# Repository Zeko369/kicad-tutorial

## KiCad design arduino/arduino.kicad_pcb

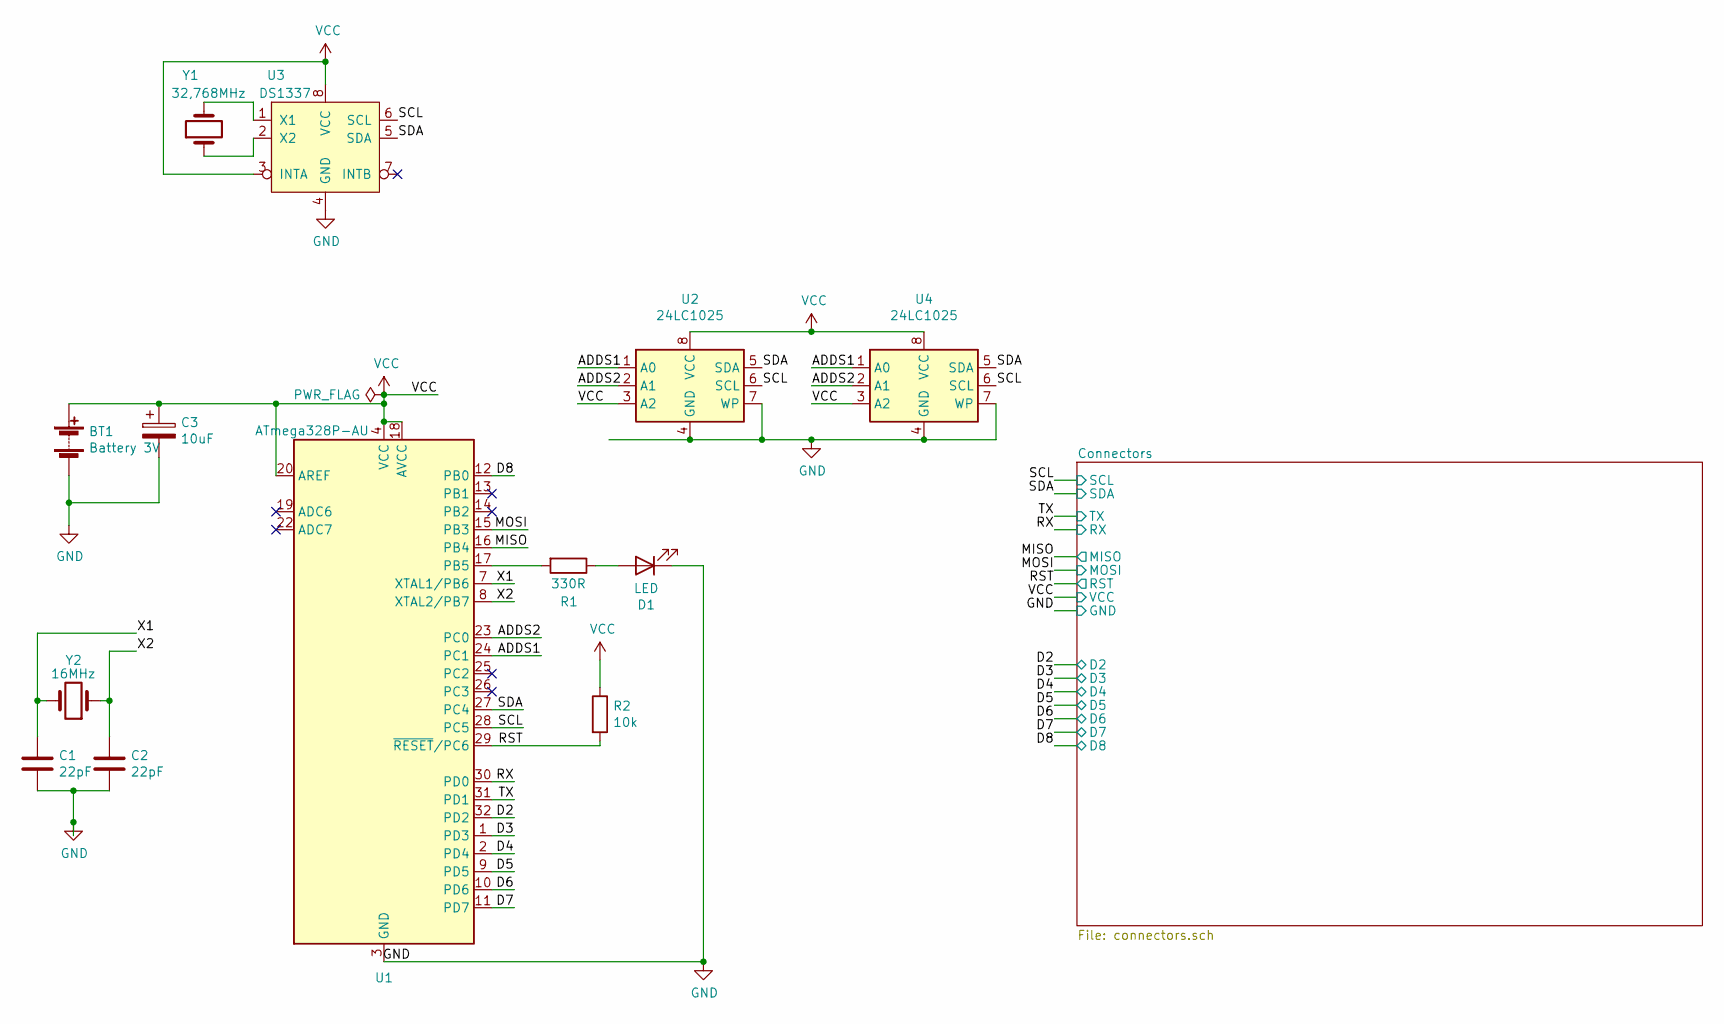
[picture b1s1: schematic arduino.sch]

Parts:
BT1: Battery 3V; PinSocket_1x02_P2.54mm_Vertical
C1, C2: 22pF; C_0805_2012Metric
C3: 10uF; CP_Elec_4x3
D1: LED; LED_0805_2012Metric
R1: 330R; R_0805_2012Metric
R2: 10k; R_0805_2012Metric
U1: ATmega328P-AU; TQFP-32_7x7mm_P0.8mm
U2, U4: 24LC1025; SOIC-8_3.9x4.9mm_P1.27mm
U3: DS1337; SO-8_5.3x6.2mm_P1.27mm
Y1: 32,768MHz; Crystal_SMD_MicroCrystal_CC7V-T1A-2Pin_3.2x1.5mm
Y2: 16MHz; Crystal_SMD_5032-2Pin_5.0x3.2mm

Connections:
/ADDS1: U1.24 (PC1), U2.1 (A0), U4.1 (A0)
/ADDS2: U1.23 (PC0), U2.2 (A1), U4.2 (A1)
/D2: U1.32 (PD2); also elsewhere on the board
/D3: U1.1 (PD3); also elsewhere on the board
/D4: U1.2 (PD4); also elsewhere on the board
/D5: U1.9 (PD5); also elsewhere on the board
/D6: U1.10 (PD6); also elsewhere on the board
/D7: U1.11 (PD7); also elsewhere on the board
/D8: U1.12 (PB0); also elsewhere on the board
/MISO: U1.16 (PB4); also elsewhere on the board
/MOSI: U1.15 (PB3); also elsewhere on the board
/RST: R2.2, U1.29 (~RESET~/PC6); also elsewhere on the board
/RX: U1.30 (PD0); also elsewhere on the board
/SCL: U1.28 (PC5), U2.6 (SCL), U3.6 (SCL), U4.6 (SCL); also elsewhere on the board
/SDA: U1.27 (PC4), U2.5 (SDA), U3.5 (SDA), U4.5 (SDA); also elsewhere on the board
/TX: U1.31 (PD1); also elsewhere on the board
/X1: C1.1, U1.7 (XTAL1/PB6), Y2.2
/X2: C2.1, U1.8 (XTAL2/PB7), Y2.1
GND: BT1.2 (-), C1.2, C2.2, C3.2, D1.1 (K), U1.3 (GND), U1.5 (GND), U1.21 (GND), U2.4 (GND), U2.7 (WP), U3.4 (GND), U4.4 (GND), U4.7 (WP); also elsewhere on the board
unnamed: D1.2 (A), R1.1
unnamed: R1.2, U1.17 (PB5)
unnamed: U3.1 (X1), Y1.2
unnamed: U3.2 (X2), Y1.1
VCC: BT1.1 (+), C3.1, R2.1, U1.4 (VCC), U1.6 (VCC), U1.18 (AVCC), U1.20 (AREF), U2.3 (A2), U2.8 (VCC), U3.3 (INTA), U3.8 (VCC), U4.3 (A2), U4.8 (VCC); also elsewhere on the board

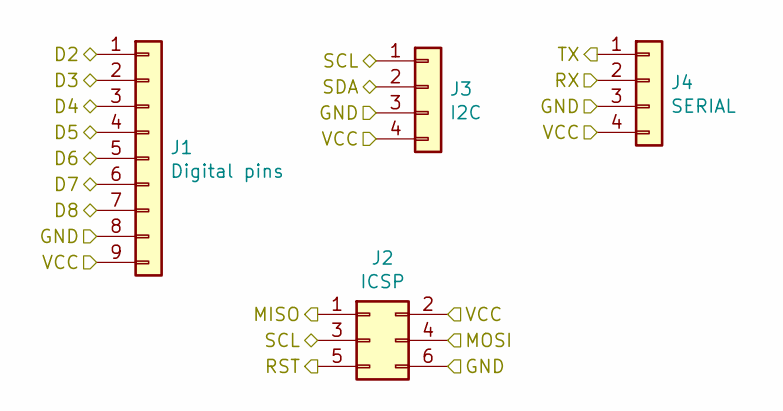
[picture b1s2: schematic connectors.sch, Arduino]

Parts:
J1: Digital pins; PinSocket_1x09_P2.54mm_Vertical
J2: ICSP; PinSocket_2x03_P2.54mm_Vertical
J3: I2C; PinSocket_1x04_P2.54mm_Vertical
J4: SERIAL; PinSocket_1x04_P2.54mm_Vertical

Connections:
/D2: J1.1; also elsewhere on the board
/D3: J1.2; also elsewhere on the board
/D4: J1.3; also elsewhere on the board
/D5: J1.4; also elsewhere on the board
/D6: J1.5; also elsewhere on the board
/D7: J1.6; also elsewhere on the board
/D8: J1.7; also elsewhere on the board
/MISO: J2.1; also elsewhere on the board
/MOSI: J2.4; also elsewhere on the board
/RST: J2.5; also elsewhere on the board
/RX: J4.2; also elsewhere on the board
/SCL: J2.3, J3.1; also elsewhere on the board
/SDA: J3.2; also elsewhere on the board
/TX: J4.1; also elsewhere on the board
GND: J1.8, J2.6, J3.3, J4.3; also elsewhere on the board
VCC: J1.9, J2.2, J3.4, J4.4; also elsewhere on the board

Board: 2 copper layers, 17 parts (0 on the bottom side), 24 nets, no tracks yet.

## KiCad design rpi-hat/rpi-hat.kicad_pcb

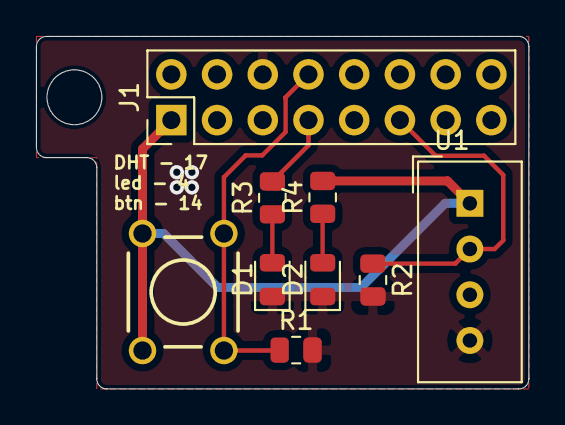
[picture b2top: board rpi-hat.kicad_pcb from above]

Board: 2 copper layers, 27.4 x 19.6 mm, 9 parts (0 on the bottom side), 7 nets.

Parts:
D1, D2: LED; LED_0805_2012Metric
J1: Raspberry_Pi_2_3; PinHeader_2x08_P2.54mm_Vertical
R1, R2: 10K; R_0805_2012Metric
R3, R4: 330R; R_0805_2012Metric
SW1: SW_DPST; SW_PUSHBUTTON_PTH
U1: DHT22; Aosong_DHT11_5.5x12.0_P2.54mm

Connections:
/3V3: J1.1, R4.2, SW1.2, U1.1
/Button: J1.8, R1.1, SW1.1
/DHT22: J1.11, R2.1, U1.2
/LED: J1.7, R3.2
GND: D1.1, D2.1, J1.6, R1.2, R2.2, U1.4
unnamed: D1.2, R3.1
unnamed: D2.2, R4.1

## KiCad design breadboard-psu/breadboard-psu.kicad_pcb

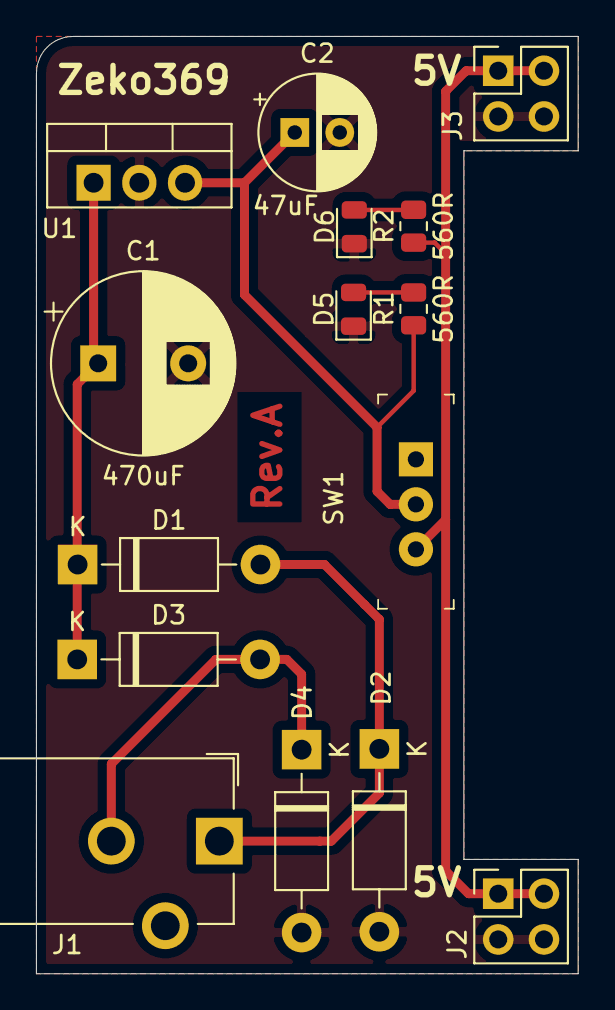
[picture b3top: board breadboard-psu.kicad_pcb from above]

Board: 2 copper layers, 30.1 x 52.1 mm, 15 parts (0 on the bottom side), 8 nets.

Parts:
C1: 470uF; CP_Radial_D10.0mm_P5.00mm
C2: 47uF; CP_Radial_D6.3mm_P2.50mm
D1, D2, D3, D4: 1N4007; D_DO-41_SOD81_P10.16mm_Horizontal
D5, D6: LED; LED_0805_2012Metric
J1: Barrel_Jack_Switch; BarrelJack_CUI_PJ-102AH_Horizontal
J2, J3: Conn_02x02_Odd_Even; PinHeader_2x02_P2.54mm_Vertical
R1, R2: 560R; R_0805_2012Metric
SW1: SW_DPDT_x2; Switch_Slide_11.6x4mm_EG1218
U1: LM7805_TO220; TO-220-3_Vertical

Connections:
/GND: C1.2, C2.2, D2.2, D4.2, D5.1, D6.1, J2.3, J2.4, J3.3, J3.4, U1.2
/IN+: D1.2, D2.1, J1.1
/IN-: D3.2, D4.1, J1.2
/VCC: J2.1, J2.2, J3.1, J3.2, R2.1, SW1.3
/VIN: C1.1, D1.1, D3.1, U1.1
/VOUT: C2.1, R1.1, SW1.2, U1.3
unnamed: D5.2, R1.2
unnamed: D6.2, R2.2

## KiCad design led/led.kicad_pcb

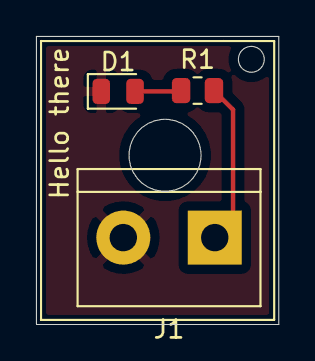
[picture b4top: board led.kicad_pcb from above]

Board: 2 copper layers, 13.5 x 16.0 mm, 3 parts (0 on the bottom side), 3 nets.

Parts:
D1: LED; LED_0805_2012Metric
J1: Conn_01x02_Female; TerminalBlock_bornier-2_P5.08mm
R1: R; R_0805_2012Metric

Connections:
+5V: J1.1, R1.1
GND: D1.1, J1.2
unnamed: D1.2, R1.2

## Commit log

2021-10-20 Init
2021-10-20 Most of initial led thingy
2021-10-21 PCB stuff
2021-10-21 Breadboard sch + board
2021-10-21 Add gerbers
2021-10-21 Rounder corners + gerbers
2021-10-21 Ignore DS_Store
2021-10-22 RPI hat project
2021-10-22 RPI finish
2021-10-22 Init arduino project
2021-10-22 Init add
2021-10-22 Create component + add
2021-10-22 Add component values
2021-10-22 Done with schematic, start PCB
2021-10-22 Layout setup
2021-10-22 Finish course
